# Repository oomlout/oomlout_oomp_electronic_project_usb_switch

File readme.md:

# Usb Switch Two to One
A simple usb switch using a re22227 chip in oobb plate_03_03 format

A simple usb switch using a re22227 chip in oobb plate_03_03 format  
* ibom github: [ibom github](kicad/current_version/working/bom/ibom.html)
* ibom direct: [ibom direct](https://raw.githack.com/oomlout/oomlout_oomp_electronic_project_usb_switch/main/kicad/current_version/working/bom/ibom.html)

## schematic  
  
[schematic (pdf)](kicad/current_version/working/working_schematic.pdf)  

## pcb  

[board (pdf)](kicad/current_version/working/working.pdf)  

## corel working

## module
* [connector_usb_micro_surface_mount](https://github.com/oomlout/oomlout_oomp_module_src/tree/main/modules/connector_usb_micro_surface_mount/working) 
* [connector_usb_micro_surface_mount](https://github.com/oomlout/oomlout_oomp_module_src/tree/main/modules/connector_usb_micro_surface_mount/working) 
* [connector_usb_a_through_hole](https://github.com/oomlout/oomlout_oomp_module_src/tree/main/modules/connector_usb_a_through_hole/working) 
* [ic_usb_multiplexer_msop_10_two_to_one_rs2227xn](https://github.com/oomlout/oomlout_oomp_module_src/tree/main/modules/ic_usb_multiplexer_msop_10_two_to_one_rs2227xn/working) 
* [logic_glue](https://github.com/oomlout/oomlout_oomp_module_src/tree/main/modules/logic_glue/working) 
* [mechanical_board_shape_oobb_plate_03_03](https://github.com/oomlout/oomlout_oomp_module_src/tree/main/modules/mechanical_board_shape_oobb_plate_03_03/working) 
* [switch_slide_single_pole_double_throw_2_8_mm_x_8_mm_x_1_4](https://github.com/oomlout/oomlout_oomp_module_src/tree/main/modules/switch_slide_single_pole_double_throw_2_8_mm_x_8_mm_x_1_4/working) 
* [switch_slide_single_pole_double_throw_2d54_header](https://github.com/oomlout/oomlout_oomp_module_src/tree/main/modules/switch_slide_single_pole_double_throw_2d54_header/working) 

## oomp_parts_summary
| index | designator | quantity | oomp_id | 
| --- | --- | --- | --- | 
| 1 | CON3 | 1 | [electronic_socket_usb_a_through_hole](https://github.com/oomlout/oomlout_oomp_part_src/tree/main/parts/electronic_socket_usb_a_through_hole/working)<br>[scuath](https://github.com/oomlout/oomlout_oomp_part_src/tree/main/parts/electronic_socket_usb_a_through_hole/working)<br>[Electronic Socket Usb A Through Hole](https://github.com/oomlout/oomlout_oomp_part_src/tree/main/parts/electronic_socket_usb_a_through_hole/working)<br>[LCSC - C2345<br>](https://lcsc.com/product-detail/C2345.html)<br> | 
| 2 | R3 | 1 | [electronic_resistor_0603_270_ohm](https://github.com/oomlout/oomlout_oomp_part_src/tree/main/parts/electronic_resistor_0603_270_ohm/working)<br>[r6o271](https://github.com/oomlout/oomlout_oomp_part_src/tree/main/parts/electronic_resistor_0603_270_ohm/working)<br>[Electronic Resistor 0603 270 Ohm](https://github.com/oomlout/oomlout_oomp_part_src/tree/main/parts/electronic_resistor_0603_270_ohm/working)<br><br>[Uniroyal - 0603WAJ0271T5E- not in jlc basic parts]() [(L)  ](https://www.lcsc.com/search?q=0603WAJ0271T5E)[(D)  ](https://www.digikey.com/en/products?keywords=0603WAJ0271T5E)[(M)  ](https://www.mouser.com/Search/Refine?Keyword=0603WAJ0271T5E)[(N)  ](https://www.newark.com/search?st=0603WAJ0271T5E)[(SZ)  ](https://so.szlcsc.com/global.html?k=0603WAJ0271T5E)<br>[Uniroyal - 0603WAF2700T5E- jlc basic part]() [(L)  ](https://www.lcsc.com/search?q=0603WAF2700T5E)[(D)  ](https://www.digikey.com/en/products?keywords=0603WAF2700T5E)[(M)  ](https://www.mouser.com/Search/Refine?Keyword=0603WAF2700T5E)[(N)  ](https://www.newark.com/search?st=0603WAF2700T5E)[(SZ)  ](https://so.szlcsc.com/global.html?k=0603WAF2700T5E)<br>[Yageo - RC0603JR-07270RL- available everywhere](https://www.yageo.com/en/Chart/Download/pdf/RC0603JR-07270RL) [(L)  ](https://www.lcsc.com/search?q=RC0603JR-07270RL)[(D)  ](https://www.digikey.com/en/products?keywords=RC0603JR-07270RL)[(M)  ](https://www.mouser.com/Search/Refine?Keyword=RC0603JR-07270RL)[(N)  ](https://www.newark.com/search?st=RC0603JR-07270RL)[(SZ)  ](https://so.szlcsc.com/global.html?k=RC0603JR-07270RL)<br> | 
| 3 | H7,H3,H4,H6 | 4 | [electronic_mounting_hole_m3](https://github.com/oomlout/oomlout_oomp_part_src/tree/main/parts/electronic_mounting_hole_m3/working)<br>[mhm3](https://github.com/oomlout/oomlout_oomp_part_src/tree/main/parts/electronic_mounting_hole_m3/working)<br>[Electronic Mounting Hole M3](https://github.com/oomlout/oomlout_oomp_part_src/tree/main/parts/electronic_mounting_hole_m3/working)<br><br> | 
| 4 | J3,J4,J1 | 3 | [electronic_header_2_54_mm_4_pin_through_hole](https://github.com/oomlout/oomlout_oomp_part_src/tree/main/parts/electronic_header_2_54_mm_4_pin_through_hole/working)<br>[hi14pth](https://github.com/oomlout/oomlout_oomp_part_src/tree/main/parts/electronic_header_2_54_mm_4_pin_through_hole/working)<br>[Electronic Header 2 54 Mm 4 Pin Through Hole](https://github.com/oomlout/oomlout_oomp_part_src/tree/main/parts/electronic_header_2_54_mm_4_pin_through_hole/working)<br><br> | 
| 5 | SW2 | 1 | [electronic_switch_slide_2_54_header_surface_mount_single_pole_double_throw](https://github.com/oomlout/oomlout_oomp_part_src/tree/main/parts/electronic_switch_slide_2_54_header_surface_mount_single_pole_double_throw/working)<br>[swsi1hs](https://github.com/oomlout/oomlout_oomp_part_src/tree/main/parts/electronic_switch_slide_2_54_header_surface_mount_single_pole_double_throw/working)<br>[Electronic Switch Slide 2 54 Header Surface Mount Single Pole Double Throw](https://github.com/oomlout/oomlout_oomp_part_src/tree/main/parts/electronic_switch_slide_2_54_header_surface_mount_single_pole_double_throw/working)<br>[LCSC - C431540<br>](https://lcsc.com/product-detail/C431540.html)<br> | 
| 6 | C1,C2 | 2 | [electronic_capacitor_0603_100_nano_farad](https://github.com/oomlout/oomlout_oomp_part_src/tree/main/parts/electronic_capacitor_0603_100_nano_farad/working)<br>[c6nf100](https://github.com/oomlout/oomlout_oomp_part_src/tree/main/parts/electronic_capacitor_0603_100_nano_farad/working)<br>[Electronic Capacitor 0603 100 Nano Farad](https://github.com/oomlout/oomlout_oomp_part_src/tree/main/parts/electronic_capacitor_0603_100_nano_farad/working)<br>[LCSC - C14663<br>](https://lcsc.com/product-detail/C14663.html)[LCSC - C30926<br>](https://lcsc.com/product-detail/C30926.html)<br>[Samsung - CL10B104KB8NNNC](https://product.samsungsem.com/mlcc/CL10B104KB8NNN.do) [(L)  ](https://www.lcsc.com/search?q=CL10B104KB8NNNC)[(D)  ](https://www.digikey.com/en/products?keywords=CL10B104KB8NNNC)[(M)  ](https://www.mouser.com/Search/Refine?Keyword=CL10B104KB8NNNC)[(N)  ](https://www.newark.com/search?st=CL10B104KB8NNNC)[(SZ)  ](https://so.szlcsc.com/global.html?k=CL10B104KB8NNNC)<br>[Yageo - CC0603KRX7R9BB104](https://www.yageo.com/en/Chart/Download/pdf/CC0603KRX7R9BB104) [(L)  ](https://www.lcsc.com/search?q=CC0603KRX7R9BB104)[(D)  ](https://www.digikey.com/en/products?keywords=CC0603KRX7R9BB104)[(M)  ](https://www.mouser.com/Search/Refine?Keyword=CC0603KRX7R9BB104)[(N)  ](https://www.newark.com/search?st=CC0603KRX7R9BB104)[(SZ)  ](https://so.szlcsc.com/global.html?k=CC0603KRX7R9BB104)<br> | 
| 7 | IC1 | 1 | [electronic_ic_msop_10_multiplexer_usb_multiplexer_two_to_one_jiangsu_runic_tech_rs2227xn](https://github.com/oomlout/oomlout_oomp_part_src/tree/main/parts/electronic_ic_msop_10_multiplexer_usb_multiplexer_two_to_one_jiangsu_runic_tech_rs2227xn/working)<br>[imsp10mpump21rs2227](https://github.com/oomlout/oomlout_oomp_part_src/tree/main/parts/electronic_ic_msop_10_multiplexer_usb_multiplexer_two_to_one_jiangsu_runic_tech_rs2227xn/working)<br>[Electronic Ic Msop 10 Multiplexer Usb Multiplexer Two To One Jiangsu Runic Tech Rs2227Xn](https://github.com/oomlout/oomlout_oomp_part_src/tree/main/parts/electronic_ic_msop_10_multiplexer_usb_multiplexer_two_to_one_jiangsu_runic_tech_rs2227xn/working)<br>[LCSC - C255478<br>](https://lcsc.com/product-detail/C255478.html)<br> | 
| 8 | H1,H5,H8 | 3 | [electronic_mounting_hole_m6](https://github.com/oomlout/oomlout_oomp_part_src/tree/main/parts/electronic_mounting_hole_m6/working)<br>[mhm6](https://github.com/oomlout/oomlout_oomp_part_src/tree/main/parts/electronic_mounting_hole_m6/working)<br>[Electronic Mounting Hole M6](https://github.com/oomlout/oomlout_oomp_part_src/tree/main/parts/electronic_mounting_hole_m6/working)<br><br> | 
| 9 | IC2 | 1 | [electronic_ic_tssop_8_multiplexer_power_multiplexer_texas_instruments_tps2113apw](https://github.com/oomlout/oomlout_oomp_part_src/tree/main/parts/electronic_ic_tssop_8_multiplexer_power_multiplexer_texas_instruments_tps2113apw/working)<br>[itssp8mpptps2113](https://github.com/oomlout/oomlout_oomp_part_src/tree/main/parts/electronic_ic_tssop_8_multiplexer_power_multiplexer_texas_instruments_tps2113apw/working)<br>[Electronic Ic Tssop 8 Multiplexer Power Multiplexer Texas Instruments Tps2113Apw](https://github.com/oomlout/oomlout_oomp_part_src/tree/main/parts/electronic_ic_tssop_8_multiplexer_power_multiplexer_texas_instruments_tps2113apw/working)<br>[LCSC - C130052<br>](https://lcsc.com/product-detail/C130052.html)<br> | 
| 10 | R1,R2 | 2 | [electronic_resistor_0603_10000_ohm](https://github.com/oomlout/oomlout_oomp_part_src/tree/main/parts/electronic_resistor_0603_10000_ohm/working)<br>[r6o103](https://github.com/oomlout/oomlout_oomp_part_src/tree/main/parts/electronic_resistor_0603_10000_ohm/working)<br>[Electronic Resistor 0603 10000 Ohm](https://github.com/oomlout/oomlout_oomp_part_src/tree/main/parts/electronic_resistor_0603_10000_ohm/working)<br>[LCSC - C25804<br>](https://lcsc.com/product-detail/C25804.html)[LCSC - C15401<br>](https://lcsc.com/product-detail/C15401.html)[LCSC - C99198<br>](https://lcsc.com/product-detail/C99198.html)<br>[Uniroyal - 0603WAJ0103T5E- not in jlc basic parts]() [(L)  ](https://www.lcsc.com/search?q=0603WAJ0103T5E)[(D)  ](https://www.digikey.com/en/products?keywords=0603WAJ0103T5E)[(M)  ](https://www.mouser.com/Search/Refine?Keyword=0603WAJ0103T5E)[(N)  ](https://www.newark.com/search?st=0603WAJ0103T5E)[(SZ)  ](https://so.szlcsc.com/global.html?k=0603WAJ0103T5E)<br>[Uniroyal - 0603WAF1002T5E- jlc basic part]() [(L)  ](https://www.lcsc.com/search?q=0603WAF1002T5E)[(D)  ](https://www.digikey.com/en/products?keywords=0603WAF1002T5E)[(M)  ](https://www.mouser.com/Search/Refine?Keyword=0603WAF1002T5E)[(N)  ](https://www.newark.com/search?st=0603WAF1002T5E)[(SZ)  ](https://so.szlcsc.com/global.html?k=0603WAF1002T5E)<br>[Yageo - RC0603JR-0710KL- available everywhere](https://www.yageo.com/en/Chart/Download/pdf/RC0603JR-0710KL) [(L)  ](https://www.lcsc.com/search?q=RC0603JR-0710KL)[(D)  ](https://www.digikey.com/en/products?keywords=RC0603JR-0710KL)[(M)  ](https://www.mouser.com/Search/Refine?Keyword=RC0603JR-0710KL)[(N)  ](https://www.newark.com/search?st=RC0603JR-0710KL)[(SZ)  ](https://so.szlcsc.com/global.html?k=RC0603JR-0710KL)<br> | 
| 11 | CON1,CON2 | 2 | [electronic_socket_usb_micro_surface_mount](https://github.com/oomlout/oomlout_oomp_part_src/tree/main/parts/electronic_socket_usb_micro_surface_mount/working)<br>[scumcsm](https://github.com/oomlout/oomlout_oomp_part_src/tree/main/parts/electronic_socket_usb_micro_surface_mount/working)<br>[Electronic Socket Usb Micro Surface Mount](https://github.com/oomlout/oomlout_oomp_part_src/tree/main/parts/electronic_socket_usb_micro_surface_mount/working)<br>[LCSC - C319160<br>](https://lcsc.com/product-detail/C319160.html)<br> | 
| 12 | SW1 | 1 | [electronic_switch_slide_2_8_mm_x_8_mm_x_1_4_mm_surface_mount_single_pole_double_throw](https://github.com/oomlout/oomlout_oomp_part_src/tree/main/parts/electronic_switch_slide_2_8_mm_x_8_mm_x_1_4_mm_surface_mount_single_pole_double_throw/working)<br>[sws2880s](https://github.com/oomlout/oomlout_oomp_part_src/tree/main/parts/electronic_switch_slide_2_8_mm_x_8_mm_x_1_4_mm_surface_mount_single_pole_double_throw/working)<br>[Electronic Switch Slide 2 8 Mm X 8 Mm X 1 4 Mm Surface Mount Single Pole Double Throw](https://github.com/oomlout/oomlout_oomp_part_src/tree/main/parts/electronic_switch_slide_2_8_mm_x_8_mm_x_1_4_mm_surface_mount_single_pole_double_throw/working)<br>[LCSC - C431540<br>](https://lcsc.com/product-detail/C431540.html)<br> | 
| 13 | C3 | 1 | [electronic_capacitor_8_mm_diameter_6_5_mm_tall_electrolytic_220_micro_farad_10_volt](https://github.com/oomlout/oomlout_oomp_part_src/tree/main/parts/electronic_capacitor_8_mm_diameter_6_5_mm_tall_electrolytic_220_micro_farad_10_volt/working)<br>[c8d65tuf220v10](https://github.com/oomlout/oomlout_oomp_part_src/tree/main/parts/electronic_capacitor_8_mm_diameter_6_5_mm_tall_electrolytic_220_micro_farad_10_volt/working)<br>[Electronic Capacitor 8 Mm Diameter 6 5 Mm Tall Electrolytic 220 Micro Farad 10 Volt](https://github.com/oomlout/oomlout_oomp_part_src/tree/main/parts/electronic_capacitor_8_mm_diameter_6_5_mm_tall_electrolytic_220_micro_farad_10_volt/working)<br>[LCSC - C249496<br>](https://lcsc.com/product-detail/C249496.html)<br> | 

Search Links: (L) - lcsc, (D) - digikey, (M) - mouser, (N) - newark, (SZ) - szlcsc
note: a work on progress that takes the bom file from kicad pcb and try's to add oomp details

## positions
### top
| # Ref | Val | Package | PosX | PosY | Rot | Side | 
| --- | --- | --- | --- | --- | --- | --- | 
| C1 | c6nf100 | c6nf100_electronic_capacitor_0603_100_nano_farad | 3.0 | 1.725 | -90.0 | top | 
| C2 | c6nf100 | c6nf100_electronic_capacitor_0603_100_nano_farad | -9.0 | -9.5 | 0.0 | top | 
| C3 | c8d65tuf220v10 | c8d65tuf220v10_electronic_capacitor_8_mm_diameter_6_5_mm_tall_electrolytic_220_micro_farad_10_volt | -7.55 | -4.0 | 0.0 | top | 
| CON1 | scumcsm | scumcsm_electronic_socket_usb_micro_surface_mount | -21.11 | 3.175 | -90.0 | top | 
| CON2 | scumcsm | scumcsm_electronic_socket_usb_micro_surface_mount | -21.11 | -11.825 | -90.0 | top | 
| CON3 | scuath | scuath_electronic_socket_usb_a_through_hole | 12.7 | -5.73 | 90.0 | top | 
| IC1 | imsp10mpump21rs2227 | imsp10mpump21rs2227_electronic_ic_msop_10_multiplexer_usb_multiplexer_two_to_one_jiangsu_runic_tech_rs2227xn | 0.0 | 0.0 | -90.0 | top | 
| IC2 | itssp8mpptps2113 | itssp8mpptps2113_electronic_ic_tssop_8_multiplexer_power_multiplexer_texas_instruments_tps2113apw | -15.0 | -4.5 | -90.0 | top | 
| J1 | hi14pth | hi14pth_electronic_header_2_54_mm_4_pin_through_hole | 19.0 | -6.0 | 180.0 | top | 
| J3 | hi14pth | hi14pth_electronic_header_2_54_mm_4_pin_through_hole | -15.5 | 6.0 | 90.0 | top | 
| J4 | hi14pth | hi14pth_electronic_header_2_54_mm_4_pin_through_hole | -12.5 | -18.5 | -90.0 | top | 
| R1 | r6o103 | r6o103_electronic_resistor_0603_10000_ohm | 2.0 | -4.0 | 0.0 | top | 
| R2 | r6o103 | r6o103_electronic_resistor_0603_10000_ohm | 2.175 | 4.5 | 0.0 | top | 
| R3 | r6o271 | r6o271_electronic_resistor_0603_270_ohm | -15.5 | 0.5 | 0.0 | top | 
| SW1 | sws2880s | sws2880s_electronic_switch_slide_2_8_mm_x_8_mm_x_1_4_mm_surface_mount_single_pole_double_throw | 0.0 | -19.5 | 0.0 | top | 
| SW2 | swsi1hs | swsi1hs_electronic_switch_slide_2_54_header_surface_mount_single_pole_double_throw | -0.04 | -7.5 | 90.0 | top | 

### bottom
no data

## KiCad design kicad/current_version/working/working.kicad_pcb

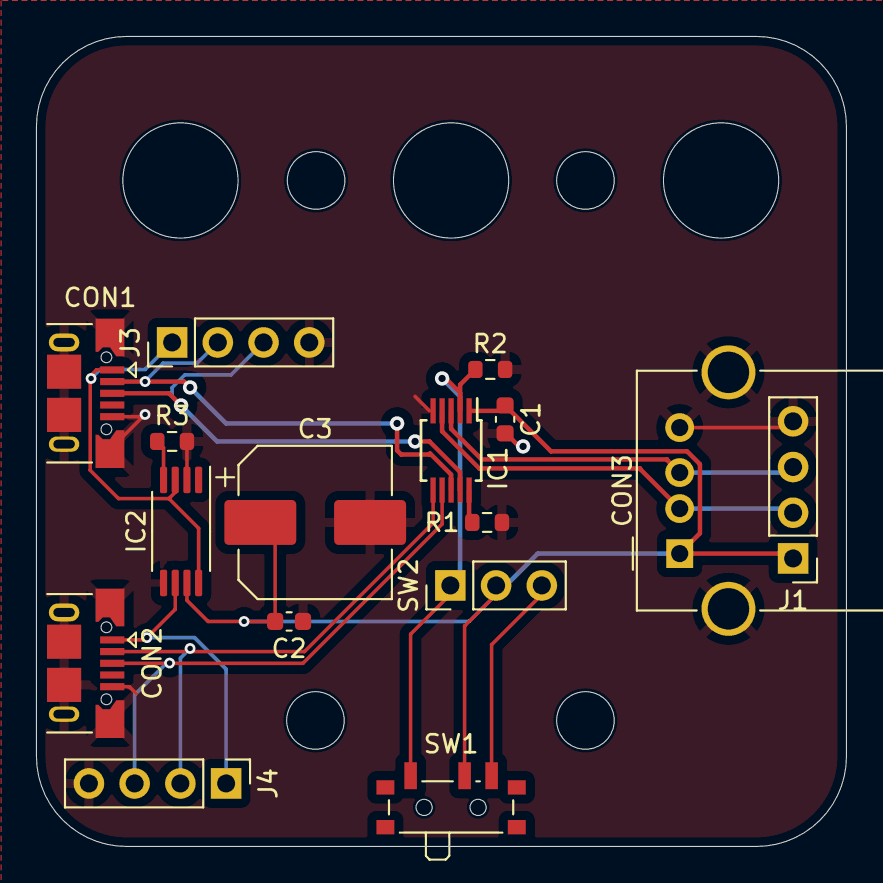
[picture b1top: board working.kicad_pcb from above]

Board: 2 copper layers, 45.0 x 45.0 mm, 23 parts (0 on the bottom side), 14 nets.

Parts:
C1, C2: c6nf100; c6nf100_electronic_capacitor_0603_100_nano_farad
C3: c8d65tuf220v10; c8d65tuf220v10_electronic_capacitor_8_mm_diameter_6_5_mm_ta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
CON1, CON2: scumcsm; scumcsm_electronic_socket_usb_micro_surface_mount
CON3: scuath; scuath_electronic_socket_usb_a_through_hole
H1, H5, H8: mhm6; mhm6_electronic_mounting_hole_m6
H3, H4, H6, H7: mhm3; mhm3_electronic_mounting_hole_m3
IC1: imsp10mpump21rs2227; imsp10mpump21rs2227_electronic_ic_msop_10_multiplexer_usb_m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
IC2: itssp8mpptps2113; itssp8mpptps2113_electronic_ic_tssop_8_multiplexer_power_mu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
J1, J3, J4: hi14pth; hi14pth_electronic_header_2_54_mm_4_pin_through_hole
R1, R2: r6o103; r6o103_electronic_resistor_0603_10000_ohm
R3: r6o271; r6o271_electronic_resistor_0603_270_ohm
SW1: sws2880s; sws2880s_electronic_switch_slide_2_8_mm_x_8_mm_x_1_4_mm_sur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
SW2: swsi1hs; swsi1hs_electronic_switch_slide_2_54_header_surface_mount_s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

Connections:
+5V: C1.1, C2.1, C3.1, CON3.1 (VBUS), IC1.1 (___v_plus), IC2.7 (___out), J1.1, SW1.2 (B), SW2.2 (B)
/5v_in_1_zz: CON1.1 (VBUS), IC2.3 (___vsns), IC2.8 (___in1), J3.1
/5v_in_2_zz: CON2.1 (VBUS), IC2.6 (___in2), J4.1
/select: IC1.2 (___s), R2.1, SW1.1 (A), SW2.1 (A)
/slide_switch_out_2: SW1.3 (C), SW2.3 (C)
/usb_negative_main: CON3.2 (D-), IC1.4 (___d_minus), J1.2
/usb_negative_secondary_1: CON2.2 (D-), IC1.6 (___hsd1_minus), J4.2
/usb_negative_secondary_2: CON1.2 (D-), IC1.8 (___hsd2_minus), J3.2
/usb_positive_main: CON3.3 (D+), IC1.3 (___d_plus), J1.3
/usb_positive_secondary_1: CON2.3 (D+), IC1.7 (___hsd1_plus), J4.3
/usb_positive_secondary_2: CON1.3 (D+), IC1.9 (___hsd2_plus), J3.3
GND: C1.2, C2.2, C3.2, CON1.5 (GND), CON1.6 (Shield), CON2.5 (GND), CON2.6 (Shield), CON3.4 (GND), CON3.5 (Shield), IC1.5 (___gnd), IC2.2 (___en), IC2.5 (___gnd), J1.4, J3.4, J4.4, R1.2, R2.2, R3.2
unnamed: IC1.10 (___oe), R1.1
unnamed: IC2.4 (___ilim), R3.1

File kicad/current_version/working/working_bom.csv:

"Id";"Designator";"Footprint";"Quantity";"Designation";"Supplier and ref";
1;"J2";"swsi1hs_electronic_switch_slide_2d54_header_surface_mount_single_pole_double_throw";1;"swsi1hs";;;
2;"CON3";"scuath_electronic_socket_usb_a_through_hole";1;"scuath";;;
3;"R3";"r6o271_electronic_resistor_0603_270_ohm";1;"r6o271";;;
4;"H7,H3,H4,H6";"mhm3_electronic_mounting_hole_m3";4;"mhm3";;;
5;"C1,C2";"c6nf100_electronic_capacitor_0603_100_nano_farad";2;"c6nf100";;;
6;"IC1";"imsp10mpump21rs2227_electronic_ic_msop_10_multiplexer_usb_multiplexer_two_to_one_jiangsu_runic_tech_rs2227xn";1;"imsp10mpump21rs2227";;;
7;"H1,H5,H8";"mhm6_electronic_mounting_hole_m6";3;"mhm6";;;
8;"IC2";"itssp8mpptps2113_electronic_ic_tssop_8_multiplexer_power_multiplexer_texas_instruments_tps2113apw";1;"itssp8mpptps2113";;;
9;"R1,R2";"r6o103_electronic_resistor_0603_10000_ohm";2;"r6o103";;;
10;"CON1,CON2";"scumcsm_electronic_socket_usb_micro_surface_mount";2;"scumcsm";;;
11;"J1";"sws2880s_electronic_switch_slide_2_8_mm_x_8_mm_x_1_4_mm_surface_mount_single_pole_double_throw";1;"sws2880s";;;
12;"C3";"c8d65tuf220v10_electronic_capacitor_8_mm_diameter_6_5_mm_tall_electrolytic_220_micro_farad_10_volt";1;"c8d65tuf220v10";;;

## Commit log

2023-09-07 commiting after auto generation
2023-09-07 initial workings
2023-09-12 first version maybe
2023-09-12 fixed schematic
2023-09-12 new docs
2023-09-12 added working_manual.yaml
2023-09-13 workings
2023-09-13 fixes
2023-09-16 added power mux
2023-09-17 production update
